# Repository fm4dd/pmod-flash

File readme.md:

## Flash PMOD

### Description

This PMOD provides the Macronix MX25R6435F SPI Flash memory in a pass-through PMOD connector board. The MX25R6435F is a	64Mbit (8MByte) Serial NOR Flash that can operate in multiple modes up to 80Mhz Quad SPI. The PMOD includes the option to install a 7-pin 2.54mm pitch testpoint header for signal and protocol analysis.

https://www.mxic.com.tw/en-us/products/NOR-Flash/Pages/Ultra-Low-Power-Flash.aspx

http://fpga.fm4dd.com/

### Schematic

### PCB Gerber

[PMOD Flash Gerber V1.0](fabfiles/v10/20230921-pmod-flash-gerber.zip)

The PMOD Flash module was designed with KiCad 7

### Pin Assignments
<table>
  <tr><th>Pinout</th><th>Pin</th><th>Function</th><th>Pin</th><th>Function</th></tr>
  <tr><td rowspan="6"></td>
        <td>1</td><td>CS</td><td>7</td><td>SIO2</td></tr>
    <tr><td>2</td><td>MOSI</td><td>8</td><td>SIO3</td></tr>
    <tr><td>3</td><td>MISO</td><td>9</td><td> not connected (CS2)</td></tr>
    <tr><td>4</td><td>SCK</td><td>10</td><td>not connected (CS3)</td></tr>
    <tr><td>5</td><td>GND</td><td>11</td><td>GND</td></tr>
    <tr><td>6</td><td>3V3</td><td>12</td><td>3V3</td></tr>
</table>

### Example Code

The following code examples demonstrate the PMOD function for quick verification on various Microcontroller and FPGA platforms.

| Platform   | Test Program location                    | Description                                                    |
|------------|------------------------------------------|----------------------------------------------------------------|
| Arduino    |[examples/arduino](examples/arduino)      | Flash test adopted from the SparkFun_SPI_SerialFlash library   |
| Raspberry  |[examples/rpi](examples/rpi)              | Linux has the flashrom program for basic read/write commands   |
| Gatemate   |[examples/gatemate](examples/gatemate)    | Gatemate FPGA test program for basic Flash access validation   |
| iCEBreaker |[examples/icebreaker](examples/icebreaker)| iCEBreaker FPGA test program for basic Flash access validation |

### PMOD-Flash Function Tests

PMOD Flash module connected to the PMOD2RPi board, driven by Seeeduino XIAO SAMD21 MCU:

PMOD Flash module connected to the PMOD2RPi board, interfacing with the Raspberry Pi 4:

PMOD Flash module verified running at 50MHz SPI clock speed with the Raspberry Pi 4:

PMOD Flash module test on Cologne Chip Gatemate FPGA:

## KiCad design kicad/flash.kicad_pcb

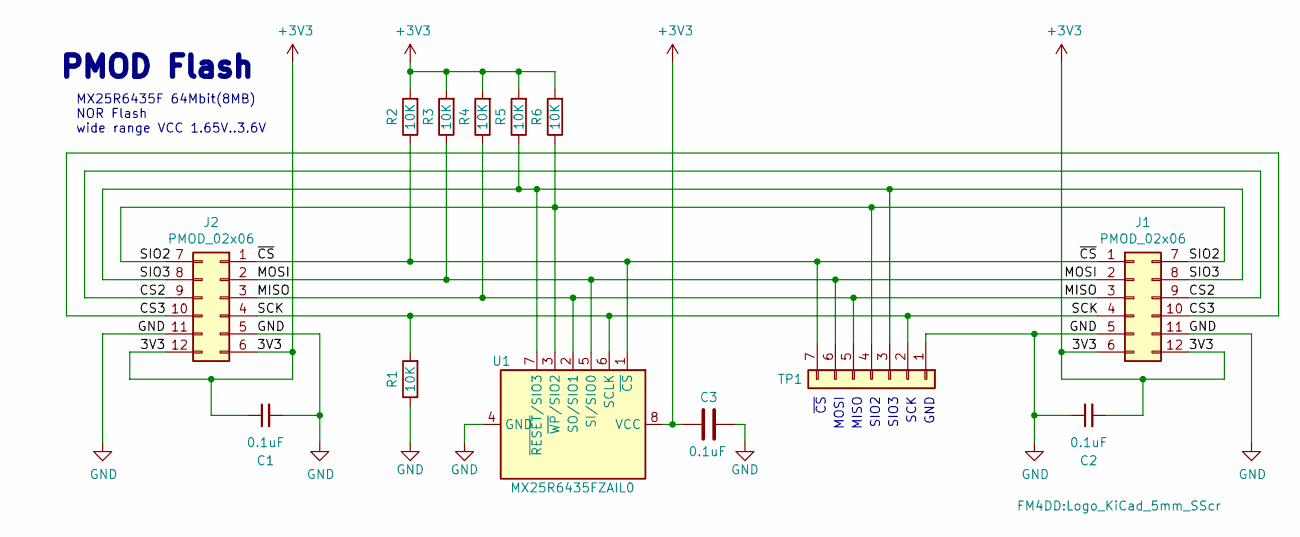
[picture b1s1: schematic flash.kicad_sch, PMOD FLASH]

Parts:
C1, C2: 0.1uF; C_0402_1005Metric
C3: 0.1uF; C_0402_1005Metric; MPN CC0402KRX7R7BB104; LCSC C327009
J1: PMOD_02x06; PMODPinSocket_2x06_P2.54mm_Horizontal
J2: PMOD_02x06; PMODHeader_2x06_P2.54mm_Horizontal
L1: Logo_KiCad_5mm; Logo_KiCad_5mm_SScr
R1, R2, R3, R4, R5, R6: 10K; R_0402_1005Metric; MPN RC0402JR-075K1L
TP1: Conn_01x07; PinHeader_1x07_P2.54mm_Vertical
U1: MX25R6435FZAIL0; USON-8_4x4mm

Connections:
+3V3: C1.1, C2.2, C3.1, J1.6, J1.12, J2.6, J2.12, R2.2, R3.2, R4.2, R5.2, R6.2, U1.8 (VCC)
/CS2: J1.9, J2.9
/CS3: J1.10, J2.10
/MISO: J1.3, J2.3, R4.1, TP1.5, U1.2 (SO/SIO1)
/MOSI: J1.2, J2.2, R3.1, TP1.6, U1.5 (SI/SIO0)
/SCK: J1.4, J2.4, R1.2, TP1.2, U1.6 (SCLK)
/SIO2: J1.7, J2.7, R6.1, TP1.4, U1.3 (~WP/SIO2)
/SIO3: J1.8, J2.8, R5.1, TP1.3, U1.7 (~RESET/SIO3)
/~CS: J1.1, J2.1, R2.1, TP1.7, U1.1 (~CS)
GND: C1.2, C2.1, C3.2, J1.5, J1.11, J2.5, J2.11, R1.1, TP1.1, U1.4 (GND), U1.9 (GND)

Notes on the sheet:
MX25R6435F 64Mbit(8MB) NOR Flash wide range VCC 1.65V..3.6V
SIO2
SCK
MISO
~{CS}
PMOD Flash
GND
SIO3
MOSI

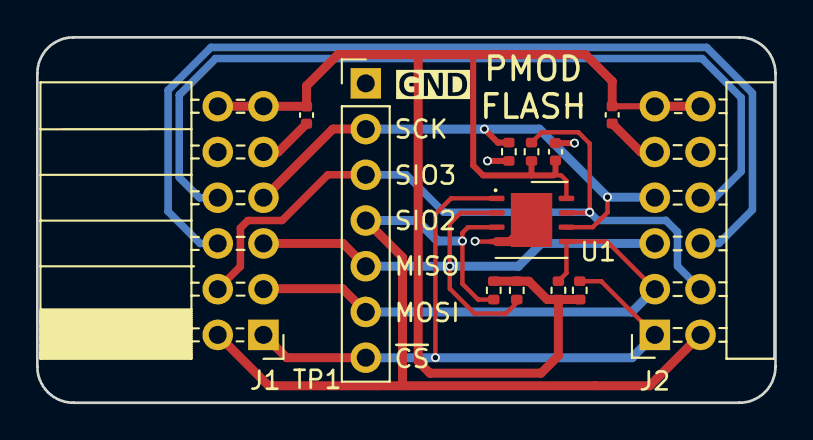
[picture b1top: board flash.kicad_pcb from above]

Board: 2 copper layers, 41.0 x 20.3 mm, 14 parts (1 on the bottom side), 10 nets.

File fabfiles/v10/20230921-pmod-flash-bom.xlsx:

Comment | Designator | Footprint | JLCPCB Part #（optional）
10K | R1,R2,R3,R4,R5,R6 | R_0402_1005Metric | C25744
0.1uF | C2,C1,C3 | C_0402_1005Metric | C1525
MX25R6435FZAIL0 | U1 | USON-8_4x4mm | C2802847

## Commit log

2023-10-01 initial check-in
2026-02-23 Add SPI flash example for Gatemate FPGA
2026-02-24 add iCEBreaker FPGA example code
2026-02-24 icebreaker example can read onboard flash

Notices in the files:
kicad/flash.kicad_pcb:
License: CC-BY-SA 4.0
